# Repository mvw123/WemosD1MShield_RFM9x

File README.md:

Wemos D1 Mini shield for RFM95 Lora
===================================

NOT COMPLETE - WORK HALTED

Lora shield for Wemos D1 mini
Used for a 1 channel lora gateway.
Eagle cad

Not fully wired or laid out due to a similar board having been made by a chap named Hallard.

Work stopped. 

Archived for future updates.

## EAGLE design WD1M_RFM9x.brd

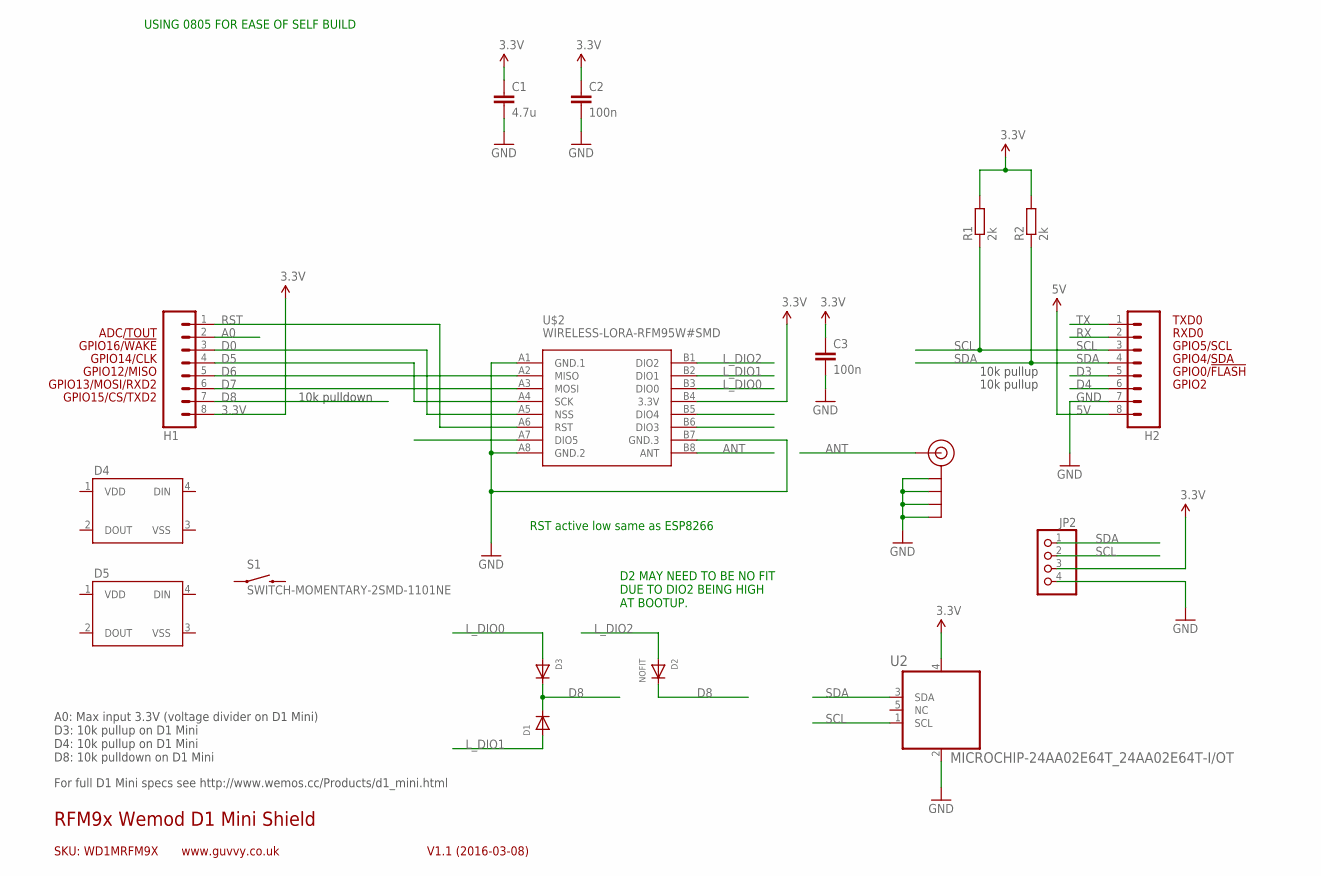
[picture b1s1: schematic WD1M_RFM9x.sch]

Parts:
C1: 4.7u; C0805K
C2, C3: 100n; C0805K
D1, D3: DIODESOD-323F; SOD-323F
D2: NOFIT; SOD-323F
D4, D5: WS2812B
H1, H2: M08; 1X08
J$2: _C2H_ANTENNATINY; _C2H_SMA_UFL_PAD_TINY
JP2: PINHD-1X4; 1X04
R1, R2: 2k; R0805
S1: SWITCH-MOMENTARY-2SMD-1101NE; TACTILE-SWITCH-1101NE
U2: MICROCHIP-24AA02E64T_24AA02E64T-I/OT; MICROCHIP-24AA02E64T_SOT95P270X145-5N
U$2: WIRELESS-LORA-RFM95W#SMD

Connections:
3.3V: C1.1, C2.1, C3.1, H1.8, JP2.3, R1.2, R2.2, U$2.B4 (3.3V)
5V: H2.8
A0: H1.2
ANT: J$2.ANT1 (SIGNAL), J$2.ANT2 (SIGNAL), J$2.ANT3 (SIGNAL), U$2.B8 (ANT)
D0: H1.3, U$2.A5 (NSS)
D3: H2.5
D4: H2.6
D5: H1.4, U$2.A4 (SCK)
D6: H1.5, U$2.A2 (MISO)
D7: H1.6, U$2.A3 (MOSI)
D8: D1.C, D2.C, D3.C, H1.7
GND: C1.2, C2.2, C3.2, H2.7, J$2.GND1 (GND), J$2.GND2 (GND), J$2.GND3 (GND), J$2.GND4 (GND), JP2.4, U2.2 (VSS), U$2.A1 (GND.1), U$2.A8 (GND.2), U$2.B7 (GND.3)
L_DIO0: D3.A, U$2.B3 (DIO0)
L_DIO1: D1.A, U$2.B2 (DIO1)
L_DIO2: D2.A, U$2.B1 (DIO2)
L_DIO3: U$2.B6 (DIO3)
L_DIO4: U$2.B5 (DIO4)
L_DIO5: U$2.A7 (DIO5)
RST: H1.1, U$2.A6 (RST)
RX: H2.2
SCL: H2.3, JP2.2, R1.1, U2.1 (SCL)
SDA: H2.4, JP2.1, R2.1, U2.3 (SDA)
TX: H2.1
VCC: U2.4 (VCC)
VDD: D4.1 (VDD), D5.1 (VDD)
VSS: D4.3 (VSS), D5.3 (VSS)

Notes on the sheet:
GPIO2
GPIO0/!FLASH
GPIO12/MISO
GPIO4/SDA
GPIO5/SCL
RXD0
TXD0
GPIO13/MOSI/RXD2
GPIO14/CLK
GPIO15/CS/TXD2
GPIO16/!WAKE
SKU: WD1MRFM9X
RFM9x Wemod D1 Mini Shield
V1.1 (2016-03-08)
www.guvvy.co.uk
ADC/TOUT
A0: Max input 3.3V (voltage divider on D1 Mini) D3: 10k pullup on D1 Mini D4: 10k pullup on D1 Mini D8: 10k pulldown on D1 Mini
10k pulldown
10k pullup
For full D1 Mini specs see http://www.wemos.cc/Products/d1_mini.html
RST active low same as ESP8266
USING 0805 FOR EASE OF SELF BUILD
D2 MAY NEED TO BE NO FIT DUE TO DIO2 BEING HIGH AT BOOTUP.

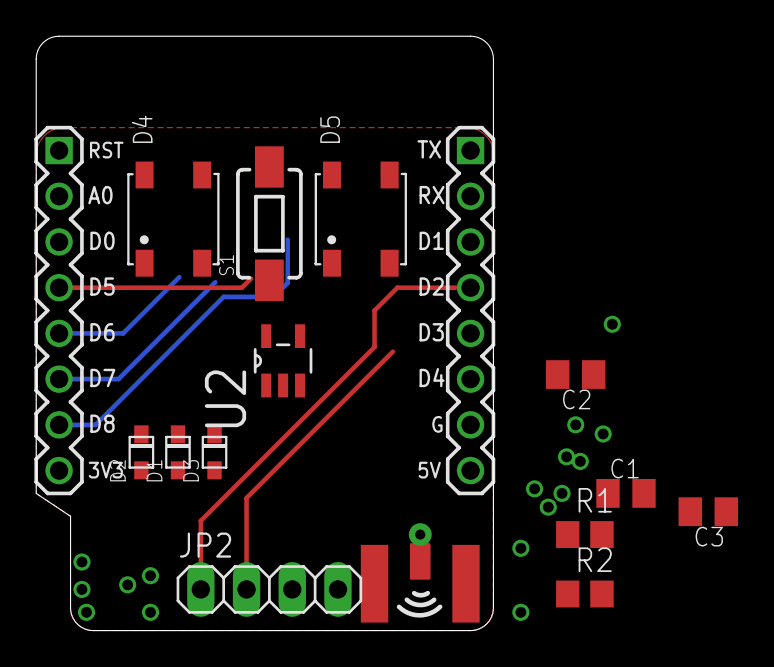
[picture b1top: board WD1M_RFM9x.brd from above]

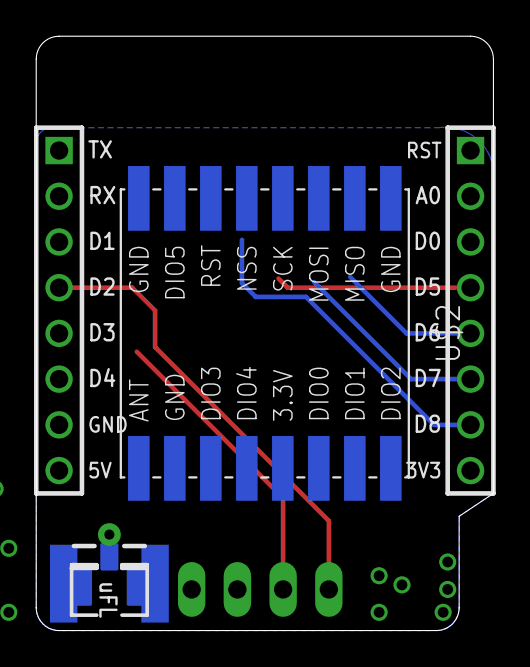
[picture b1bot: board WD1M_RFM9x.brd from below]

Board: 2 copper layers, 25.4 x 33.0 mm, 17 parts (2 on the bottom side), 16 nets.

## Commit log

2017-11-08 Incomplete RFM9x shield for Wemos D1 Mini
    Incomplete RFM9x shield for Wemos D1 Mini. work put on hold due to a
    design already existing by a chap named Hallard.
2017-11-08 minor update
2017-11-09 Work halted, Minor updates before archiving
2017-11-09 minor text formatting
2017-11-26 FIT/NOFIT change

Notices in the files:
parts and their libraries:
freetronics-original: Licensing: CC v3.0 Share-Alike You are welcome to use this library for commercial purposes.
diy-modules: Released under the Creative Commons Attribution 4.0 International License: http://creativecommons.org/licenses/by/4.0
